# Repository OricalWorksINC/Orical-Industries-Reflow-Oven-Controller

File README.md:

Reflow Oven Controller
====================
Big Thanks to Ed Simmons <ed@estechnical.co.uk> , Karl Pitrich <karl@pitrich.com>
For all there hard work on the original code that this is based on.

**News**
New method of prosscesing for better performance!
Adding Serial for co-processor to process the steppers and other calculations and operations

 NEW HARDWARE COMING SOON AND FIRMWARE REVISIONS FOR TUNNLE OVENS!

**Arduino-based reflow oven controller with:**
* [PID] loop control
* [Wave Packet] and [Phase Fired] control for AC outputs
* graphic TFT LC-Display, drawing the temperature curves
  * using an [Adafruit 1.8" TFT] or derivate display
* solely controlled using a cheap rotary encoder and its single button
* stores up to 30 temperature profiles in EEPROM
* configurable PID-parameters
* simple, small hardware to drive loads up to 600V and up to 8A
* hardware can
  * measure two temperatures independently
  * drive two AC loads, such as heater and fan
* could also be used for slow coockers
* *Please Note*: Requires Arduino IDE 1.5.x or newer

(c) 2016 John Reichard <john@hobbywizards.com>
in part based on a project (c) 2013 Ed Simmons <ed@estechnical.co.uk> , (c) 2014 Karl Pitrich <karl@pitrich.com>

**Post action shot**

![CycleWithOverflow] | ![Warning]
------------ | -------------

## Warning: This project operates with possibly lethal mains voltage. If you are unsure what to do, don't do it and get help from an experienced tinkerer with professional training.

**Completed build**

![Completed1] | ![Completed2]
------------ | -------------

Introduction
====================

This Reflow Oven Controller relies on an [Arduino Pro Micro], which is similar to the Leonardo and easily obtainable on eb*y for less than $10, plus my custom shield, which is actually more like a motherboard.

As I believe it is not wise to have a mess of wiring and tiny breakout-boards for operating mains powered equipment, I've decided to design custom board with easily obtainable components.

The hardware can be found in the [folder hardware], including the Eagle schematics and PCB layout files. It should fit the freemium version of Eagle. Here are preview images:

![PCB][ImgPCB]
![Schematic][ImgSCH]

From my manufacturing run, I have some spare PCBs and parts. They are available at my [tindie store].

The board contains the [Arduino Pro Micro], very simple [Zero crossing] detection circuit, used to align control logic to mains frequency, two [MAX31855] thermocouple-to-digital converters and two [Sharp S202S01] PCB-mount solid state relays, mounted on cheap [Fischer SK409 50,8] heat sinks. The current software uses only one of the thermocouples, so you need to populate one IC only. If you're lucky, you can get free samples of the MAX31855 from Maxim.

The software uses [PID] control of the heater and fan output for improved temperature stability. The heater AC load is controlled using [Wave Packet] control in order to minimize RF interference and load on the relay. For the fan motor, [Phase Fired] control has been implemented.

Please note that all important timings are *based on the mains frequency*, so the circuit will **not work** properly without mains connection.

But for testing, I've added an additional timer to simulate the zero-crossings, in order to run the software without being connected to mains. The software should work in 50 and 60Hz mains, the 60Hz version is not tested, though.

Errata and construction infos
========

Issue | Notes
------------ | -------------

Code can only be uploded with the Arduino 1.0.6 IDE or the LCD won't dysplay anything in my case.

Screenshots and usage information
========

Image | Information
------------ | -------------
![CycleWithOverflow] | *Display after a cylcle has been completed. The blue line is the setpoint, the red line the actual temperature measured by the thermocouple. Note that the graph wraps around automatically. 'Sp' is the current setpoint calculated by the PID loop. In the lower line there are: Current heater and fan outputs, both in percent, and the current temperature rise or drop rate in °C per second. The graph will draw orientation lines every 50°C up to the peak temperature set in the selected profile.*
![MenuDefault] | *The main menu can be navigated by rotating the encoder (sic!). Clicking enters the menu item, or navigates to the submenu. Doubleclick moves up or back or exits the menu item.*
![FanSpeedEdit] | *To edit a setting, click once to enter edit mode (red cursor), then rotate to change the value, click again to save. Doubleclick will exit without saving.*
![MenuEditProfile] | -
![ProfileSettings] | *Typical solder profile settings...*
![ProfileSettingsEdit] | *These parameters can be easily edited using the encoder as described above.*
![MenuLoadProfile] | *Up to 30 Profiles can be loaded and saved. You have to do this manually, so that you can have 'save-as' functionality without overwriting existing profiles.*
![PIDValues] | *Current pid values for my 1300W 20$ toaster oven.*
![PIDValuesEdit] | *Editing is simple, like above. Note that, unlike with the profile settings, the PID values will be automatically stored to EEPROM when you exit the submenu by doubleclicking.*

Obtaining the source code
====================

Get the code using `git`.

	git clone https://github.com/OricalWorksINC/reflowOvenController

or [download a Snapshot].

I've added some libraries I've used as submodules to the git repositroy, so it is important that, after cloning this repository, you do 

    git submodule update --init

to fetch all involved libraries. (See: [Submodule Cheat Sheet])

Installation
====================

Of course, you need to have the Arduino IDE installed. I've worked with version 1.5.x only and I will not support older versions. Get it from the [Arduino Download] page or upgrade you current Arduino setup.

There as several dependencies you need to install. 

If you are unfamiliar with Arduino Libraries, please read [the library guide].
Basically, each library needs to be liked or copied into your Arduino library folder.

On a Mac, this is how you link the submodule libraries to your Arduino libraries folder:

    cd ~/Documents/Arduino/Libraries
    ln -s ~/Development/<reflow source code>/libraries
    
My code uses [TimerOne] for basic timing, for the 1.8" TFT I've used [Adafruit_ST7735], which requires [Adafruit_GFX]. I **strongly suggest** to use my **modified version** of [Adafruit_ST7735-pit], as it **performs much better**, but requires you to use SPI, which my board does anyway.

For the user interface you require my own [Menu] and [ClickEncoder] libraries, which are included as submodules.

All other libraries need to be downloaded and installed.

After you've installed all libraries, open the Arduino IDE, open the ReflowController.pde sketch (using File->Open).

Select the right hardware from the Tools->Board menu. (Use Leonardo for the Pro Micro)

Compile the firmware (Sketch->Verify) to test everything is installed correctly. If something's wrong, feel free to post an issue here on github, I will look into it.

Now, choose the correct serial port from Tools->Serial Port and then upload the code.
*Remember* that a standard compile will get stuck at "Calibrating..." without proper mains connection, so that zero crossing interrupts can occur.

I could not fit PID Autotuning into the limited space of the Arduino in addition the normal code. So if you want to try to autotune you PID Loop, install the [PID_AutoTune] Library, `#define PIDTUNE 1` in the .ino file, then recompile and download do the Arduino.

As all timing relies on Zero Crossing detection, you need to `#define FAKE_HW 1` and install [TimerThree] when you want to run without actual hardware *and/or* without mains connection.

Things to note
====================

* The [MAX31855] does not like the thermocouple being grounded; It must be isolated from ground or earth.
* The PID Loop must be tuned individually for each oven. It will *not* work out of the box. 
* [PID Autotune] is not very useful, as it seems to be able to tune only to keep a specific temperature value, which is not what we do in a reflow oven. Also, at least my oven seems to be very non-linear when heating up.
* When rewiring inside your oven, use only wiring that can withstand high temperatures. I use silicone coated lace.
* Do not solder wiring inside you oven, the temperature might desolder you joints. **Crimp everything.**
* Use proper earth ground connection for your ovens chassis.
* 

 ******** How To Upgrade Arduino For Faster Speeds! *********
 
 To boost your Arduino Uno's performance up to 25% faster, all you have to do is replace the 16 MHz crystal with 20 MHz crystal, and update the bootloader with one that designed for this upgraded speed (see instruction below).
 
 Please note that this is NOT overclocking, we'll just tuning it to maximum speed allowed by manufacturer as stated in ATmega328 datasheet. So it's 100% safe and guaranteed to run as reliable as before, it's just 25% faster :) up to nearly 20 MIPS!
Step 1: Add following content to your boards.txt (located in hardware/arduino sub-directory of the Arduino application directory, i.e. \Program Files (x86)\Arduino\hardware\arduino in default installation path on 64-bit Windows (or \Program Files\Arduino\hardware\arduino if you're still using the immortal WinXP ;)...

##############################################################

atmega328_20.name=Arduino Uno++ 20MHz

atmega328_20.upload.protocol=stk500
atmega328_20.upload.maximum_size=30720
atmega328_20.upload.speed=57600

atmega328_20.bootloader.low_fuses=0xFF
atmega328_20.bootloader.high_fuses=0xDA
atmega328_20.bootloader.extended_fuses=0x05
atmega328_20.bootloader.path=atmega
atmega328_20.bootloader.file=ATmega328_20MHz.hex
atmega328_20.bootloader.unlock_bits=0x3F
atmega328_20.bootloader.lock_bits=0x0F

atmega328_20.build.mcu=atmega328p
atmega328_20.build.f_cpu=20000000L
atmega328_20.build.core=arduino

----------------- End Of Code ----------------

Step 2: Create new file with name ATmega328_20MHz.hex under hardware/arduino/bootloaders/atmega sub-directory with following content:

------------- Start Of Code --------------

:107800000C94343C0C94513C0C94513C0C94513CE1
:107810000C94513C0C94513C0C94513C0C94513CB4
:107820000C94513C0C94513C0C94513C0C94513CA4
:107830000C94513C0C94513C0C94513C0C94513C94
:107840000C94513C0C94513C0C94513C0C94513C84
:107850000C94513C0C94513C0C94513C0C94513C74
:107860000C94513C0C94513C11241FBECFEFD8E036
:10787000DEBFCDBF11E0A0E0B1E0ECE8FFE702C061
:1078800005900D92A230B107D9F712E0A2E0B1E065
:1078900001C01D92AD30B107E1F70E94313D0C945B
:1078A000C43F0C94003C982F92959F709A30B8F08A
:1078B000292F295A8F708A3078F0982F995A809101
:1078C000C00085FFFCCF2093C6008091C00085FFDB
:1078D000FCCF9093C6000895982F905DF0CF292F8C
:1078E000205DE8CF982F8091C00085FFFCCF90935A
:1078F000C6000895EF92FF920F931F93EE24FF248A
:1079000087018091C00087FD17C00894E11CF11C1D
:10791000011D111D81EDE81682E1F80683E10807DB
:1079200080E0180770F3E0910401F09105010995DA
:107930008091C00087FFE9CF8091C6001F910F9111
:10794000FF90EF9008950E947A3C982F8091C0009C
:1079500085FFFCCF9093C600913628F4903308F051
:107960009053892F08959755892F08951F930E944A
:10797000A33C182F0E94A33C1295107F810F1F91EA
:1079800008951F93182F882321F00E947A3C1150EC
:10799000E1F71F9108951F93182F0E947A3C8032BF
:1079A00049F0809103018F5F809303018530C1F01E
:1079B0001F9108958091C00085FFFCCF84E18093E2
:1079C000C6008091C00085FFFCCF1093C600809157
:1079D000C00085FFFCCF80E18093C6001F91089511
:1079E000E0910401F091050109951F9108950E940D
:1079F0007A3C803241F0809103018F5F80930301D4
:107A0000853081F008958091C00085FFFCCF84E12E
:107A10008093C6008091C00085FFFCCF80E18093F9
:107A2000C6000895E0910401F091050109950895BB
:107A300044EF51E08823A1F02D9A28EE33E0FA01BB
:107A40003197F1F721503040D1F72D9828EE33E0EF
:107A5000FA013197F1F721503040D1F7815061F7A9
:107A600008953F924F925F926F927F928F929F9272
:107A7000AF92BF92CF92DF92EF92FF920F931F933C
:107A8000CF93DF93000084E18093C4001092C5007F
:107A900088E18093C10086E08093C2005098589A94
:107AA000259A81E00E94183D24E1F22E9EE1E92E04
:107AB00085E9D82E0FE0C02E10E1B12EAA24A394A0
:107AC000B1E49B2EA6E58A2EF2E57F2EE0E26E2E33
:107AD00079E4572E63E5462E50E5352E0E947A3C18
:107AE0008033B1F18133B9F1803409F46FC081344E
:107AF00009F476C0823409F485C0853409F488C05D
:107B0000803531F1823521F1813511F1853509F466
:107B100085C0863509F48DC0843609F496C0843753
:107B200009F403C1853709F472C1863709F466C0C8
:107B3000809103018F5F80930301853079F6E09196
:107B40000401F091050109950E947A3C803351F6B9
:107B50000E94F73CC3CF0E947A3C803249F7809163
:107B6000C00085FFFCCFF092C6008091C00085FF69
:107B7000FCCF9092C6008091C00085FFFCCF809220
:107B8000C6008091C00085FFFCCF7092C600809136
:107B9000C00085FFFCCF6092C6008091C00085FFC9
:107BA000FCCF5092C6008091C00085FFFCCF409270
:107BB000C6008091C00085FFFCCF3092C600809146
:107BC000C00085FFFCCFB092C60088CF0E947A3CEF
:107BD000863808F4BDCF0E947A3C0E94F73C7ECFE5
:107BE0000E947A3C803809F49CC0813809F40BC1AA
:107BF000823809F430C1883909F48FC080E00E94CE
:107C0000CB3C6CCF84E10E94C13C0E94F73C66CF24
:107C100085E00E94C13C0E94F73C60CF0E947A3C04
:107C2000809306010E947A3C809307010E94F73CF2
:107C300055CF0E947A3C803309F411C183E00E9441
:107C4000C13C80E00E94CB3C49CF0E947A3C8093AB
:107C500009020E947A3C8093080280910C028E7F78
:107C600080930C020E947A3C853409F409C180910A
:107C7000080290910902892B89F000E010E00E942F
:107C80007A3CF801E85FFE4F80830F5F1F4F8091C1
:107C90000802909109020817190788F30E947A3C9C
:107CA000803209F045CF80910C0280FFF5C06091D1
:107CB000060170910701660F771F709307016093AB
:107CC0000601A0910802B09109021097C9F0E8E0FE
:107CD000F1E09B01AD014E0F5F1FF999FECF32BD60
:107CE00021BD819180BDFA9AF99A2F5F3F4FE41729
:107CF000F50799F76A0F7B1F7093070160930601E0
:107D00008091C00085FFFCCFF092C6008091C0003A
:107D100085FFFCCFB092C600E1CE83E00E94CB3C51
:107D2000DDCE82E00E94CB3CD9CE0E947A3C80938B
:107D300009020E947A3C809308028091060190918A
:107D40000701880F991F90930701809306010E94F5
:107D50007A3C853409F49AC080910C028E7F80931E
:107D60000C020E947A3C803209F0B8CE8091C000AB
:107D700085FFFCCFF092C600A0910802B0910902E5
:107D80001097C1F180910C02082F0170182F1695E1
:107D90001170E0910601F0910701AF014F5F5F4F55
:107DA000BA0120E030E00023B1F4112339F49491BA
:107DB0008091C00085FFFCCF9093C6002F5F3F4F9E
:107DC000CB010196FA012A173B0780F4BC014F5FF3
:107DD0005F4F002351F3F999FECFF2BDE1BDF89A50
:107DE00090B58091C00085FFFCCFE6CF709307016E
:107DF000609306018091C00085FDE5CE8091C000B2
:107E000085FFF8CFE0CE81E00E94CB3C67CE0E9498
:107E10007A3C803209F08CCE8091C00085FFFCCF87
:107E2000F092C6008091C00085FFFCCFE092C600B2
:107E30008091C00085FFFCCFD092C6008091C00029
:107E400085FFFCCFC092C6008091C00085FFFCCFAB
:107E5000B092C60043CE80E10E94CB3C3FCE0E9450
:107E60007A3C0E947A3C182F0E947A3C112309F434
:107E700083C0113009F484C08FE00E94CB3C2ECE29
:107E800080910C02816080930C02F1CE80910C02F3
:107E9000816080930C0265CF809107018823880F51
:107EA000880B8A2180930B02809106019091070133
:107EB000880F991F90930701809306018091080213
:107EC00080FF09C080910802909109020196909369
:107ED000090280930802F894F999FECF1127E091E6
:107EE0000601F0910701C8E0D1E08091080290916D
:107EF0000902103091F40091570001700130D9F35C
:107F000003E000935700E89500915700017001309D
:107F1000D9F301E100935700E89509901990009179
:107F2000570001700130D9F301E000935700E89544
:107F30001395103498F0112700915700017001300B
:107F4000D9F305E000935700E895009157000170C0
:107F50000130D9F301E100935700E895329602977A
:107F600009F0C7CF103011F00296E5CF11248091AF
:107F7000C00085FFC5CEC8CE8EE10E94CB3CAECD01
:0C7F800085E90E94CB3CAACDF894FFCF0D
:027F8C00800073
:040000030000780081
:00000001FF

--------- End of Code ---------

Step 3: desolder the old 16 Mhz crystal from Arduino Uno board. Please note that this action may void your warranty, please proceed on your own risk! If you're unsure with this, perhaps it's better to build a brand new Arduino compatible board by your own from scratch. For example, you can buy Playduino-One kit from Play-Zone — they ship worldwide — for Fr. 19.9 (about USD 21). If you live in Indonesia, you can also purchase Playduino-One Kit from azTech for only Rp150.000,- (less than USD 14).
Step 4: Install a 20 MHz crystal. Soldering should be easy since space on bottom surface is sparse.
Step 5: Burn the bootloader: open Arduino IDE, if you've done step #1 correctly then a new board should be appear under Tools > Board menu with name Arduino Uno++ 20MHz. Select the new board, attach USB cable to Arduino (or ISP programmer if you build Playduino One), and execute Tools > Burn Bootloader command. That's all, now you have a much faster Arduino!

Licensing
====================
```
The MIT License (MIT)

Copyright (c) 2016 JohnReichard
All rights reserved.

Permission is hereby granted, free of charge, to any person obtaining a copy
of this software and associated documentation files (the "Software"), to deal
in the Software without restriction, including without limitation the rights
to use, copy, modify, merge, publish, distribute, sublicense, and/or sell
copies of the Software, and to permit persons to whom the Software is
furnished to do so, subject to the following conditions:

The above copyright notice and this permission notice shall be included in
all copies or substantial portions of the Software.

THE SOFTWARE IS PROVIDED "AS IS", WITHOUT WARRANTY OF ANY KIND, EXPRESS OR
IMPLIED, INCLUDING BUT NOT LIMITED TO THE WARRANTIES OF MERCHANTABILITY,
FITNESS FOR A PARTICULAR PURPOSE AND NONINFRINGEMENT. IN NO EVENT SHALL THE
AUTHORS OR COPYRIGHT HOLDERS BE LIABLE FOR ANY CLAIM, DAMAGES OR OTHER
LIABILITY, WHETHER IN AN ACTION OF CONTRACT, TORT OR OTHERWISE, ARISING FROM,
OUT OF OR IN CONNECTION WITH THE SOFTWARE OR THE USE OR OTHER DEALINGS IN
THE SOFTWARE.
```

[PID Autotune]:https://github.com/br3ttb/Arduino-PID-AutoTune-Library
[Submodule Cheat Sheet]:http://blog.jacius.info/git-submodule-cheat-sheet/
[ESTechnical]:http://www.estechnical.co.uk
[Arduino Download]:http://arduino.cc/en/Main/Software
[folder hardware]:https://github.com/0xPIT/reflowOvenController/tree/master/hardware
[download a Snapshot]:https://github.com/0xPIT/reflowOvenController/archive/master.zip
[the library guide]:http://arduino.cc/en/Guide/Libraries
[PID]:http://en.wikipedia.org/wiki/PID_controller
[Wave Packet]:http://de.wikipedia.org/wiki/Schwingungspaketsteuerung
[Phase Fired]:http://en.wikipedia.org/wiki/Phase-fired_controllers 
[Adafruit 1.8" TFT]:http://www.adafruit.com/products/358
[MAX31855]:http://www.maximintegrated.com/en/products/analog/sensors-and-sensor-interface/MAX31855.html
[Fischer SK409 50,8]:http://www.pollin.de/shop/dt/NzE5OTY1OTk-
[Sharp S202S01]:http://sharp-world.com/products/device/lineup/data/pdf/datasheet/s102s01_e.pdf
[Zero crossing]:http://en.wikipedia.org/wiki/Zero_crossing
[TimerOne]:http://playground.arduino.cc/Code/Timer1
[TimerThree]:http://playground.arduino.cc/Code/Timer1
[Adafruit_ST7735]:https://github.com/adafruit/Adafruit-ST7735-Library
[Adafruit_GFX]:https://github.com/adafruit/Adafruit-GFX-Library
[Adafruit_ST7735-pit]:https://github.com/0xPIT/Adafruit-ST7735-Library
[Menu]:https://github.com/0xPIT/menu
[ClickEncoder]:https://github.com/0xPIT/encoder
[Arduino Pro Micro]:https://www.sparkfun.com/products/12640
[tindie store]:https://www.tindie.com/products/0xPIT/reflow-oven-controller-motherboard-for-arduino-pro-micro/

[CycleWithOverflow]:https://raw.githubusercontent.com/0xPIT/reflowOvenController/master/images/CycleWithOverflow.jpg
[FanSpeedEdit]:https://raw.githubusercontent.com/0xPIT/reflowOvenController/master/images/FanSpeedEdit.jpg
[MenuDefault]:https://raw.githubusercontent.com/0xPIT/reflowOvenController/master/images/Menu.jpg
[MenuLoadProfile]:https://raw.githubusercontent.com/0xPIT/reflowOvenController/master/images/MenuLoadProfile.jpg
[MenuEditProfile]:https://raw.githubusercontent.com/0xPIT/reflowOvenController/master/images/MenuEditProfile.jpg
[PIDValuesEdit]:https://raw.githubusercontent.com/0xPIT/reflowOvenController/master/images/PIDValuesEdit.jpg
[ProfileSettings]:https://raw.githubusercontent.com/0xPIT/reflowOvenController/master/images/ProfileSettings.jpg
[PIDValues]:https://raw.githubusercontent.com/0xPIT/reflowOvenController/master/images/PIDValues.jpg
[ProfileSettingsEdit]:https://raw.githubusercontent.com/0xPIT/reflowOvenController/master/images/ProfileSettingsEdit.jpg

[Warning]:http://www.proshieldsafetysigns.co.uk/signs/59793_signs.jpg
[ImgPCB]:https://raw.githubusercontent.com/0xPIT/reflowOvenController/master/hardware/v0.2.brd.preview.png
[ImgSCH]:https://raw.githubusercontent.com/0xPIT/reflowOvenController/master/hardware/v0.2.sch.preview.png

[ImgMissingTrace]:https://raw.githubusercontent.com/0xPIT/reflowOvenController/master/images/MissingTrace.jpg
[Completed1]:https://raw.githubusercontent.com/0xPIT/reflowOvenController/master/images/Completed1.jpg
[Completed2]:https://raw.githubusercontent.com/0xPIT/reflowOvenController/master/images/Completed2.jpg

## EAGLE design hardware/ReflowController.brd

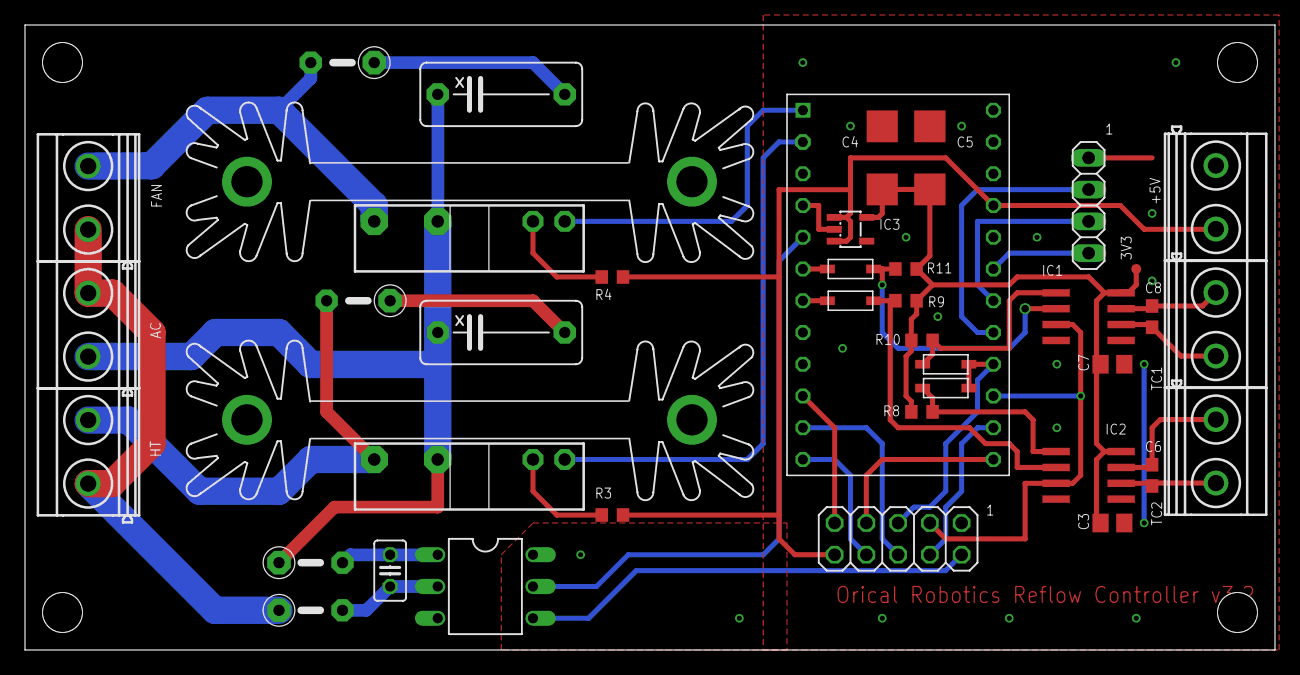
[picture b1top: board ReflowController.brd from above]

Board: 2 copper layers, 100.0 x 50.0 mm, 41 parts (0 on the bottom side), 36 nets.

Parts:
3V3: TPTP08R; TP08R
A1: ARDUINO_PRO_NANO
AC: MKDSN1,5/2-5,08
C1, C2: 100n; XC10B5
C3, C7: 100n; C0805
C4, C5: 10µ; C/6032-28R
C6, C8: 10n; C0603
C9: 100n; C025-025X050
D1, D2, D3, D4: SOD-123
ENC: 1X04
FAN: MKDSN1,5/2-5,08
HT: MKDSN1,5/2-5,08
IC1, IC2: MAX31855; SOIC8
IC3: LP298XS; SOT23-5L
K1, K2: S202S01; S102S01
KK1, KK2: SK104-PAD
LCD: 2X05
OC1: H11A1M; DIL06
R1, R2: 100R; 0207/5V
R3, R4: 120R; R0603
R5, R6: 47k; 0207/5V
R8, R9, R10, R11: 10k; R0603
TC1, TC2: MKDSN1,5/2-5,08
VCC: MKDSN1,5/2-5,08

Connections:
+3V3: 3V3.TP, C3.1, C4.+, C5.+, C7.1, IC1.4, IC2.4, IC3.5, R8.2, R9.2, R10.2, R11.2
AC1: AC.1, C1.1, C2.1, K1.2, K2.2, R5.1
AC2: AC.2, FAN.1, HT.1, R6.1
AC_OUT1: HT.2, K1.1, R1.2
AC_OUT2: FAN.2, K2.1, R2.2
GND: A1.P$3, A1.P$4, A1.P$23, C3.2, C4.-, C5.-, C7.2, ENC.1, IC1.1, IC2.1, IC3.2, LCD.1, LCD.2, OC1.4, VCC.1
LCD_CS: A1.P$13, LCD.7
LCD_DC: A1.P$12, LCD.8
LCD_RESET: A1.P$11, LCD.6
MISO: A1.P$15, IC1.7, IC2.7, LCD.3
MOSI: A1.P$14, LCD.4
unnamed: C8.2, IC1.2, TC1.2
unnamed: C6.2, IC2.2, TC2.2
unnamed: C6.1, IC2.3, TC2.1
unnamed: A1.P$17, ENC.2
unnamed: A1.P$18, ENC.3
unnamed: C1.2, R1.1
unnamed: C2.2, R2.1
unnamed: A1.P$19, ENC.4
unnamed: C9.1, OC1.1, R5.2
unnamed: C9.2, OC1.2, R6.2
unnamed: C8.1, IC1.3, TC1.1
unnamed: K1.3, R3.2
unnamed: K2.3, R4.2
unnamed: D2.A, IC2.6, R9.1
unnamed: D1.A, IC2.5, R8.1
unnamed: D4.A, IC1.6, R11.1
unnamed: D3.A, IC1.5, R10.1
SCK: A1.P$16, D1.C, D3.C, LCD.5
SD_CS: A1.P$10, LCD.9
SSR1: A1.P$2, K1.4
SSR2: A1.P$1, K2.4
TC1_CS: A1.P$6, D4.C
TC2_CS: A1.P$7, D2.C
VCC: A1.P$21, IC3.1, IC3.3, LCD.10, R3.1, R4.1, VCC.2
ZEROX: A1.P$5, OC1.5

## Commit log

2016-07-05 Updated libraries and code
2016-07-05 Updated Libraries and Code
    Refreshing code stage
2016-07-05 Updated Code and Libraries
2016-07-06 UPDATED FIRMWARE HARDWARE AND NEWS !!!
    UPDATED FIRMWARE HARDWARE AND NEWS !!!
2016-07-06 updated info
2016-07-06 Info Update
2016-07-06 Big Thanks
2016-07-08 Updated issues
2016-07-08 Faster processing How To for Arduino
2016-07-08 Faster processing and better performance How To for Arduino
2016-07-08 Updated Code and some modifications to the libraries
2016-07-08 Added How to for upgraded arduino
2016-07-08 Updated Code for Main Menu
    Updated Code for Main Menu
2016-07-08 Fixed Menu Bug
2016-07-11 Just some updates
2016-07-12 Adding Serial
    // Adding Serial for co-processor to process the steppers and other
    calculations and operations
2016-07-12 Serial
    Serial
2016-07-12 some serial updates for starting heat cycle
2016-08-25 ADDED 32 bit Version WNC
    ADDED 32 bit Version WNC
